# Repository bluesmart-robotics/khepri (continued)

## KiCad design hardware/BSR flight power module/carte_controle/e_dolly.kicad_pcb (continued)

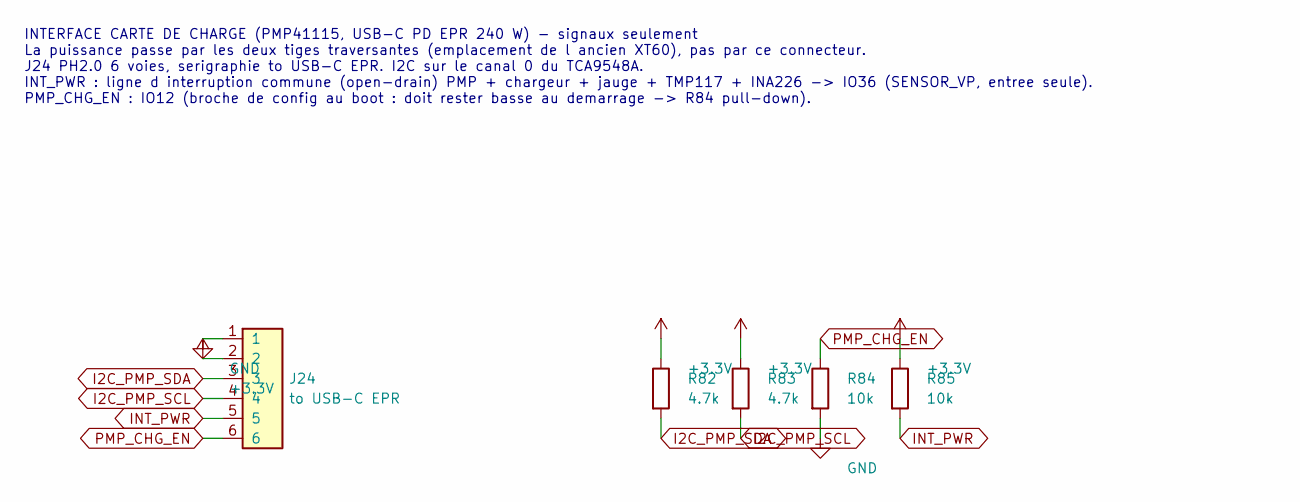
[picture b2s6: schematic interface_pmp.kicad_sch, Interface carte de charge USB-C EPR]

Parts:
J24: to USB-C EPR; JST_PH_B6B-PH-SM4-TB_1x06-1MP_P2.00mm_Vertical
R82, R83: 4.7k; R_0603_1608Metric
R84, R85: 10k; R_0603_1608Metric

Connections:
+3.3V: J24.2, R82.1, R83.1, R85.1; also elsewhere on the board
GND: J24.1, R84.2; also elsewhere on the board
I2C_PMP_SCL: J24.4, R83.2; also elsewhere on the board
I2C_PMP_SDA: J24.3, R82.2; also elsewhere on the board
INT_PWR: J24.5, R85.2; also elsewhere on the board
PMP_CHG_EN: J24.6, R84.1; also elsewhere on the board

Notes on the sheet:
INTERFACE CARTE DE CHARGE (PMP41115, USB-C PD EPR 240 W) - signaux seulement La puissance passe par les deux tiges traversantes (emplacement de l ancien XT60), pas par ce connecteur. J24 PH2.0 6 voies, serigraphie to USB-C EPR. I2C sur le canal 0 du TCA9548A. INT_PWR : ligne d interruption commune 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

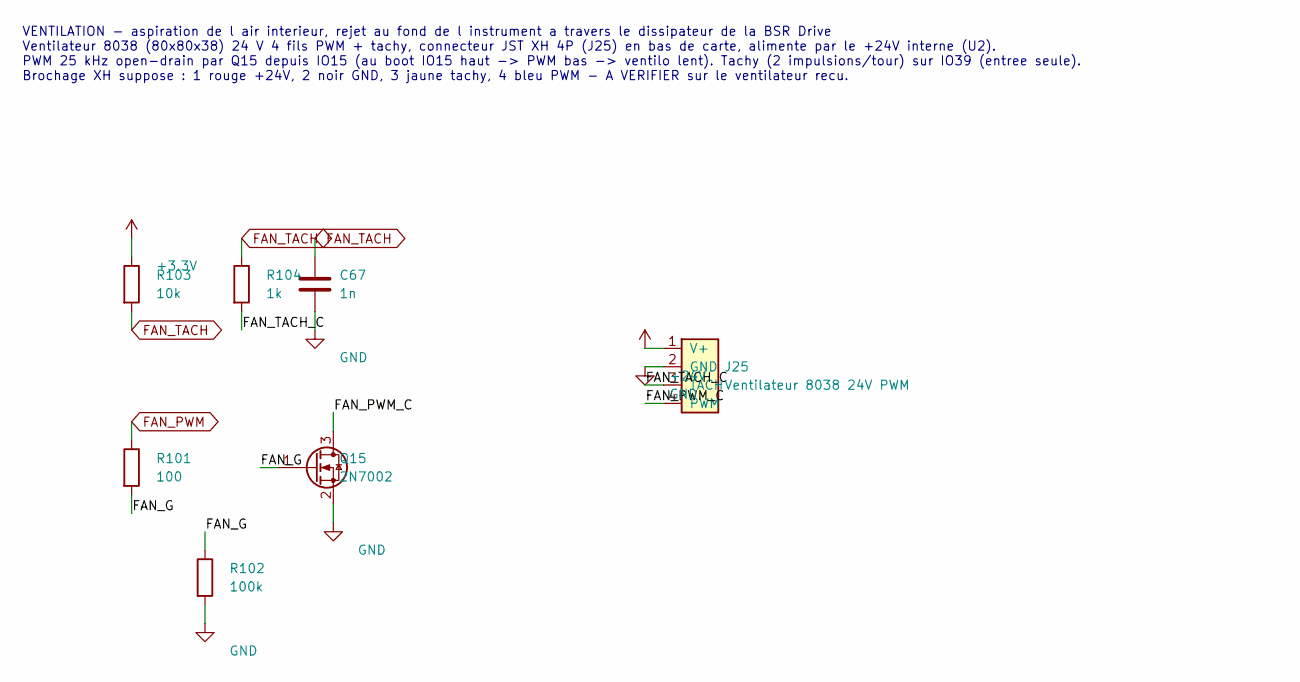
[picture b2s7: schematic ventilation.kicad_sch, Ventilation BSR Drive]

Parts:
C67: 1n; C_0603_1608Metric
J25: Ventilateur 8038 24V PWM; JST_XH_B4B-XH-A_1x04_P2.50mm_Vertical
Q15: 2N7002; SOT-23
R101: 100; R_0603_1608Metric
R102: 100k; R_0603_1608Metric
R103: 10k; R_0603_1608Metric
R104: 1k; R_0603_1608Metric

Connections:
+3.3V: R103.1; also elsewhere on the board
+24V: J25.1 (V+); also elsewhere on the board
/Ventilation/FAN_G: Q15.1 (G), R101.2, R102.1
/Ventilation/FAN_PWM_C: J25.4 (PWM), Q15.3 (D)
/Ventilation/FAN_TACH_C: J25.3 (TACH), R104.2
FAN_PWM: R101.1; also elsewhere on the board
FAN_TACH: C67.1, R103.2, R104.1; also elsewhere on the board
GND: C67.2, J25.2 (GND), Q15.2 (S), R102.2; also elsewhere on the board

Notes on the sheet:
VENTILATION - aspiration de l air interieur, rejet au fond de l instrument a travers le dissipateur de la BSR Drive Ventilateur 8038 (80x80x38) 24 V 4 fils PWM + tachy, connecteur JST XH 4P (J25) en bas de carte, alimente par le +24V interne (U2). PWM 25 kHz open-drain par Q15 depuis IO15 (au boot 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

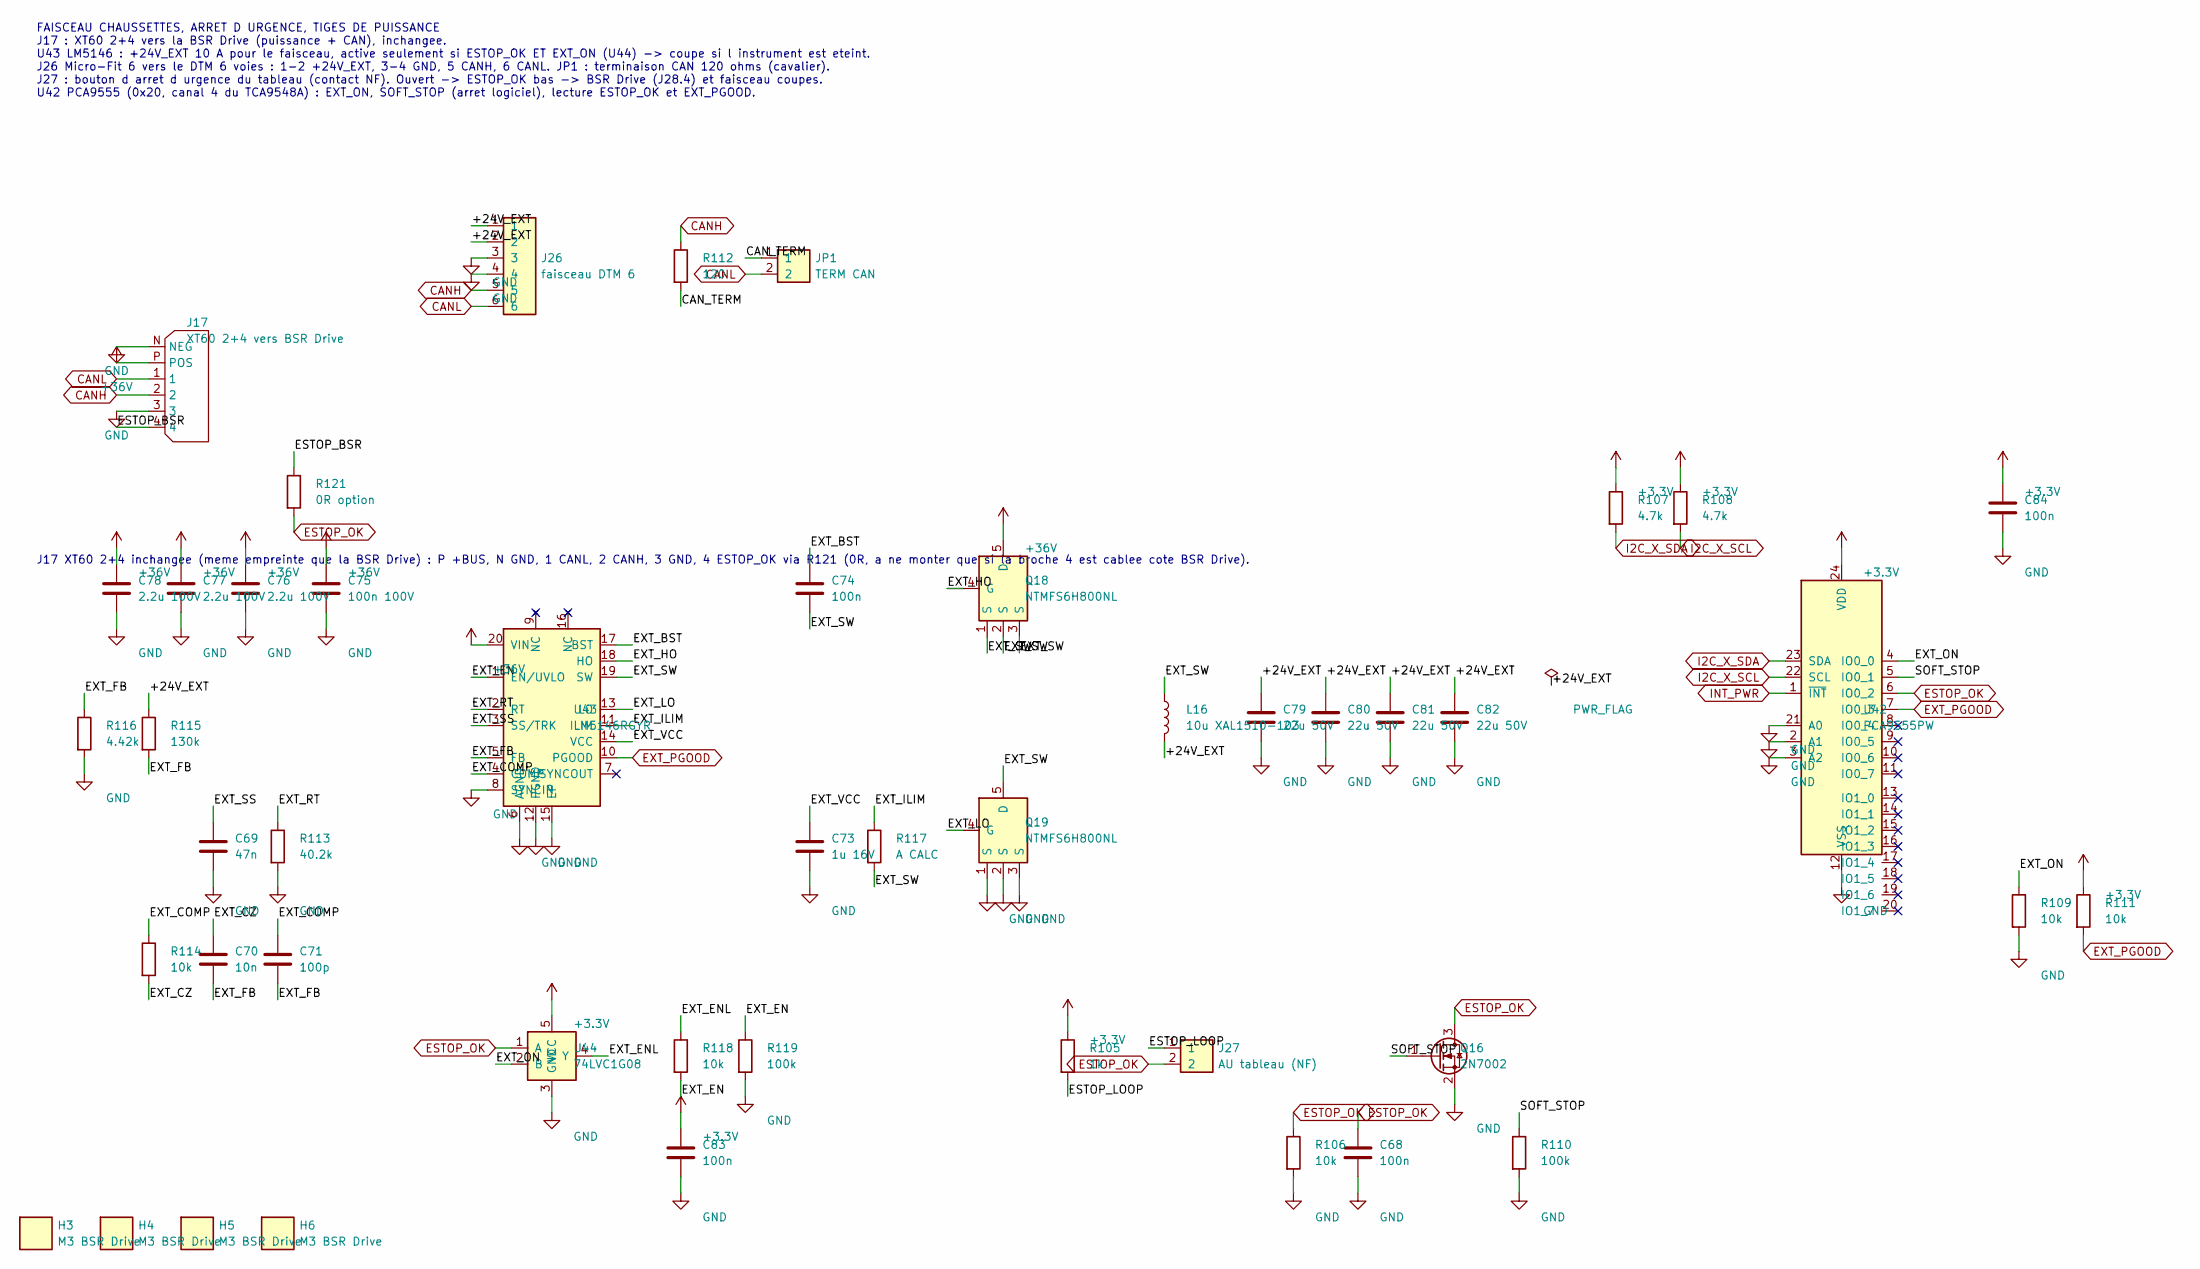
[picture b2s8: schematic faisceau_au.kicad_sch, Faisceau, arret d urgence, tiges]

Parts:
C68, C74, C83, C84: 100n; C_0603_1608Metric
C69: 47n; C_0603_1608Metric
C70: 10n; C_0603_1608Metric
C71: 100p; C_0603_1608Metric
C73: 1u 16V; C_0603_1608Metric
C75: 100n 100V; C_0603_1608Metric
C76, C77, C78: 2.2u 100V; C_1210_3225Metric
C79, C80, C81, C82: 22u 50V; C_1210_3225Metric
H3, H4, H5, H6: M3 BSR Drive; MountingHole_3.2mm_M3
J17: XT60 2+4 vers BSR Drive; AMASS_XT60-F (2+4)
J26: faisceau DTM 6; Molex_Micro-Fit_3.0_43045-0612_2x03_P3.00mm_Vertical
J27: AU tableau (NF); JST_PH_B2B-PH-SM4-TB_1x02-1MP_P2.00mm_Vertical
JP1: TERM CAN; PinHeader_1x02_P2.54mm_Vertical
L16: 10u XAL1510-103; L_Coilcraft_XAL1510-103
Q16: 2N7002; SOT-23
Q18, Q19: NTMFS6H800NL; ONSemi_SO-8FL_488AA
R105: 1k; R_0603_1608Metric
R106, R109, R111, R114, R118: 10k; R_0603_1608Metric
R107, R108: 4.7k; R_0603_1608Metric
R110, R119: 100k; R_0603_1608Metric
R112: 120; R_0603_1608Metric
R113: 40.2k; R_0603_1608Metric
R115: 130k; R_0603_1608Metric
R116: 4.42k; R_0603_1608Metric
R117: A CALC; R_0603_1608Metric
R121: 0R option; R_0603_1608Metric
U42: PCA9555PW; TSSOP-24_4.4x7.8mm_P0.65mm
U43: LM5146RGYR; Texas_RGY_R-PVQFN-N20_EP2.05x3.05mm
U44: 74LVC1G08; SOT-23-5

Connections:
+3.3V: C83.1, C84.1, R105.1, R107.1, R108.1, R111.1, U42.24 (VDD), U44.5 (VCC); also elsewhere on the board
+36V: C75.1, C76.1, C77.1, C78.1, J17.P (POS), Q18.5 (D), U43.20 (VIN); also elsewhere on the board
/Faisceau AU tiges/+24V_EXT: C79.1, C80.1, C81.1, C82.1, J26.1, J26.2, L16.2, R115.1
/Faisceau AU tiges/CAN_TERM: JP1.1, R112.2
/Faisceau AU tiges/ESTOP_BSR: J17.4, R121.1
/Faisceau AU tiges/ESTOP_LOOP: J27.1, R105.2
/Faisceau AU tiges/EXT_BST: C74.1, U43.17 (BST)
/Faisceau AU tiges/EXT_COMP: C71.1, R114.1, U43.4 (COMP)
/Faisceau AU tiges/EXT_CZ: C70.1, R114.2
/Faisceau AU tiges/EXT_EN: R118.2, R119.1, U43.1 (EN/UVLO)
/Faisceau AU tiges/EXT_ENL: R118.1, U44.4 (Y)
/Faisceau AU tiges/EXT_FB: C70.2, C71.2, R115.2, R116.1, U43.5 (FB)
/Faisceau AU tiges/EXT_HO: Q18.4 (G), U43.18 (HO)
/Faisceau AU tiges/EXT_ILIM: R117.1, U43.11 (ILIM)
/Faisceau AU tiges/EXT_LO: Q19.4 (G), U43.13 (LO)
/Faisceau AU tiges/EXT_ON: R109.1, U42.4 (IO0_0), U44.2 (B)
/Faisceau AU tiges/EXT_RT: R113.1, U43.2 (RT)
/Faisceau AU tiges/EXT_SS: C69.1, U43.3 (SS/TRK)
/Faisceau AU tiges/EXT_SW: C74.2, L16.1, Q18.1 (S), Q18.2 (S), Q18.3 (S), Q19.5 (D), R117.2, U43.19 (SW)
/Faisceau AU tiges/EXT_VCC: C73.1, U43.14 (VCC)
/Faisceau AU tiges/SOFT_STOP: Q16.1 (G), R110.1, U42.5 (IO0_1)
CANH: J17.2, J26.5, R112.1; also elsewhere on the board
CANL: J17.1, J26.6, JP1.2; also elsewhere on the board
ESTOP_OK: C68.1, J27.2, Q16.3 (D), R106.1, R121.2, U42.6 (IO0_2), U44.1 (A)
EXT_PGOOD: R111.2, U42.7 (IO0_3), U43.10 (PGOOD)
GND: C68.2, C69.2, C73.2, C75.2, C76.2, C77.2, C78.2, C79.2, C80.2, C81.2, C82.2, C83.2, C84.2, J17.3, J17.N (NEG), J26.3, J26.4, Q16.2 (S), Q19.1 (S), Q19.2 (S), Q19.3 (S), R106.2, R109.2, R110.2, R113.2, R116.2, R119.2, U42.2 (A1), U42.3 (A2), U42.12 (VSS), U42.21 (A0), U43.6 (AGND), U43.8 (SYNCIN), U43.12 (PGND), U43.15 (EP), U43.21, U44.3 (GND); also elsewhere on the board
I2C_X_SCL: R108.2, U42.22 (SCL); also elsewhere on the board
I2C_X_SDA: R107.2, U42.23 (SDA); also elsewhere on the board
INT_PWR: U42.1 (~INT); also elsewhere on the board

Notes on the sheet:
FAISCEAU CHAUSSETTES, ARRET D URGENCE, TIGES DE PUISSANCE J17 : XT60 2+4 vers la BSR Drive (puissance + CAN), inchangee. U43 LM5146 : +24V_EXT 10 A pour le faisceau, active seulement si ESTOP_OK ET EXT_ON (U44) -> coupe si l instrument est eteint. J26 Micro-Fit 6 vers le DTM 6 voies : 1-2 +24V_EXT,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
J17 XT60 2+4 inchangee (meme empreinte que la BSR Drive) : P +BUS, N GND, 1 CANL, 2 CANH, 3 GND, 4 ESTOP_OK via R121 (0R, a ne monter que si la broche 4 est cablee cote BSR Drive).

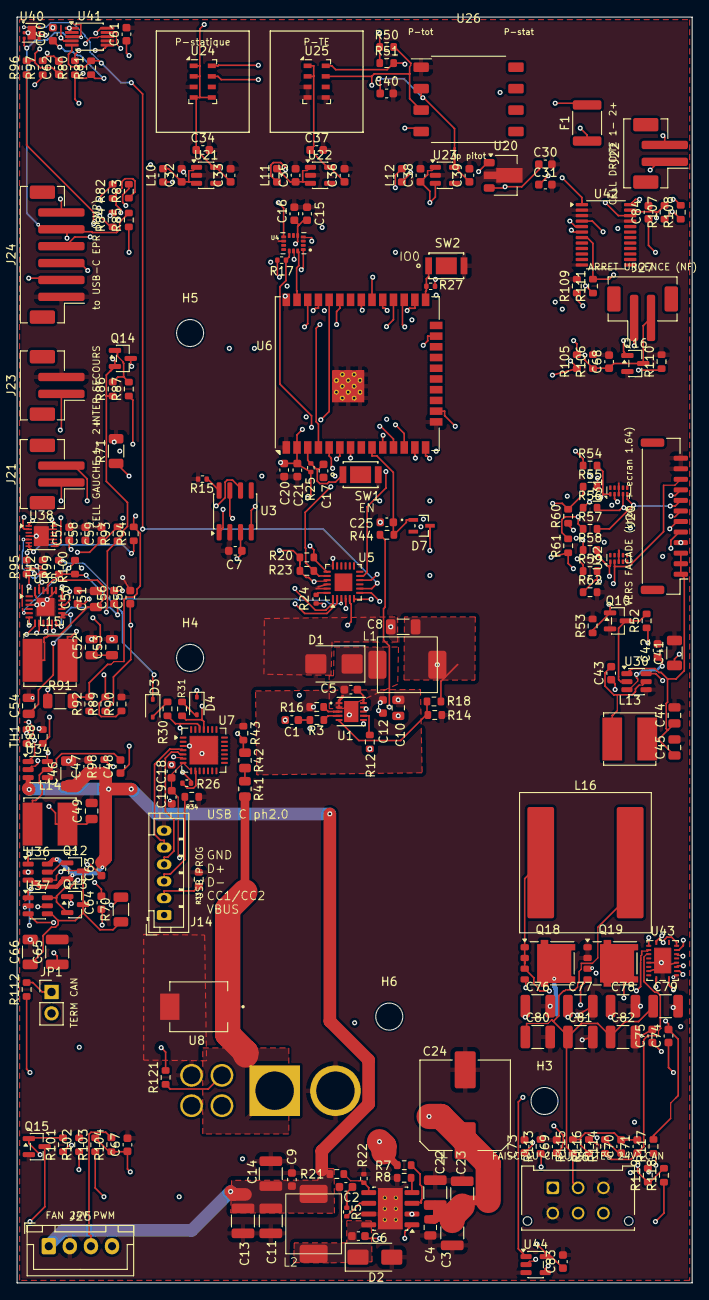
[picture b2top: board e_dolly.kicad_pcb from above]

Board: 4 copper layers, 80.0 x 150.0 mm, 231 parts (1 on the bottom side), 142 nets.

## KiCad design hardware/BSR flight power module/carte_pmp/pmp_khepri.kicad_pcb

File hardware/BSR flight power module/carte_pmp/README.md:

# Carte de charge PMP — version KHEPRI empilable

Chargeur USB-C EPR 240 W dérivé du design TI **PMP41115** (TPS26750 + BQ25756),
repris du dépôt `bluesmart-robotics/batterie` (`chargeur_pmp41115/`, Altium) et
converti en KiCad 9 pour être empilé au-dessus de la carte de contrôle et de la
BSR Drive. **Le dépôt `batterie` n'est pas modifié** (E-dolly garde sa version).

## Ce qui a été fait (04/11/2026)

1. **Import Altium → KiCad** (`PMP41115.PcbDoc`, importeur Altium de KiCad),
   puis ouverture et sauvegarde en KiCad 9.
2. **Bloc PMP tourné de −90°** et placé dans le contour de la pile : bloc
   d'origine 103 × 47 mm maintenant en x 134,5 → 181,3, y 31,0 → 134,0. Le
   connecteur USB-C J1 est en haut, à ≈ 7 mm du bord haut (bord à y 28,85).
   L'ancien contour Altium est conservé sur la couche `User.9` comme repère.
3. **Contour agrandi à 80 × 150 mm**, **même repère que la carte de contrôle**
   (x 104 → 184, y 28,85 → 178,85) : les deux fichiers KiCad se superposent
   sans décalage.
4. **XT60 2+4 J7**, même empreinte et **même position que J17 de la carte de
   contrôle** (138,125 ; 156,075), côté dessous (B.Cu). Liaison bidirectionnelle
   vers le pack : P = `BAT` (sortie/entrée batterie du BQ25756), N et broche 3 =
   GND, broches 1, 2, 4 (CAN, ESTOP) non reliées sur cette carte.
   Liaison en pistes de 1,5 mm (BAT sur B.Cu ≈ 23 mm, GND) : **à remplacer
   par des zones de cuivre** pour 5 A permanents.
5. **Connecteur de communication J8**, JST PH 6 voies (même empreinte que J24
   de la carte de contrôle, même position x 108,75 ; y 57), câble court entre
   les deux cartes :

   | J8 | Signal carte de contrôle (J24) | Net sur la PMP |
   |---|---|---|
   | 1 | GND | GND |
   | 2 | +3,3 V | `3V3_CTRL` — **non relié** (ne pas raccorder au LDO_3V3 de la PMP) |
   | 3 | SDA canal 0 | `I2Ct_SDA` (I²C cible du TPS26750, comme J6) |
   | 4 | SCL canal 0 | `I2Ct_SCL` |
   | 5 | INT_PWR | `~{I2Ct_IRQ}` (drain ouvert) |
   | 6 | CHG_EN | `CHG_EN` — **non relié** : choisir la broche (EN du BQ25756, ILIM_HIZ ou GPIO du TPS26750) |

6. **Trous M3** H11 à H15 aux positions des trous de la BSR Drive qui tombent
   hors du bloc PMP : (124,53 ; 66,30), (124,53 ; 104,80), (124,53 ; 147,30),
   (148,13 ; 147,30), (166,53 ; 157,30). Les trous BSR (148,13 ; 66,30) et
   (148,13 ; 104,80) tombent dans le bloc PMP et n'ont pas été percés (choix
   validé : garder le routage puissance d'origine).

## À reprendre par l'ingénieur

1. **Schéma** : il reste en Altium dans le dépôt `batterie`. J7, J8, H11–H15 et
   leurs nets n'existent que dans ce PCB. À reporter dans un schéma (ou importer
   les SchDoc dans KiCad) avant toute mise à jour schéma → PCB.
2. **Erreurs d'import Altium à vérifier contre le PcbDoc d'origine** (DRC KiCad :
   ≈ 1 060 erreurs, aucune ne vient des ajouts ci-dessus) :
   - pastilles « complex pad stack » non importées correctement : pastilles
     thermiques sans net de Q4, Q5, Q6, Q7 et U5 → 81 « courts-circuits »
     avec les vias VSYS, P_OUT, SW1, SW2 ;
   - 199 vias 0,3/0,2 mm d'Altium hors des règles par défaut de KiCad
     (diamètre, anneau) : ajuster les règles ou les vias ;
   - U8.5 (GND) et U1.28/29 (PP5V) non reliés après import.
3. Remplacer les pistes BAT / GND de J7 par des zones, ajouter des vias en
   parallèle.
4. Raccorder J8.2 et J8.6 (tableau ci-dessus).
5. Modèles 3D des composants : non repris de l'Altium, le STEP de cette carte
   ne montre que le circuit nu et les composants ajoutés.

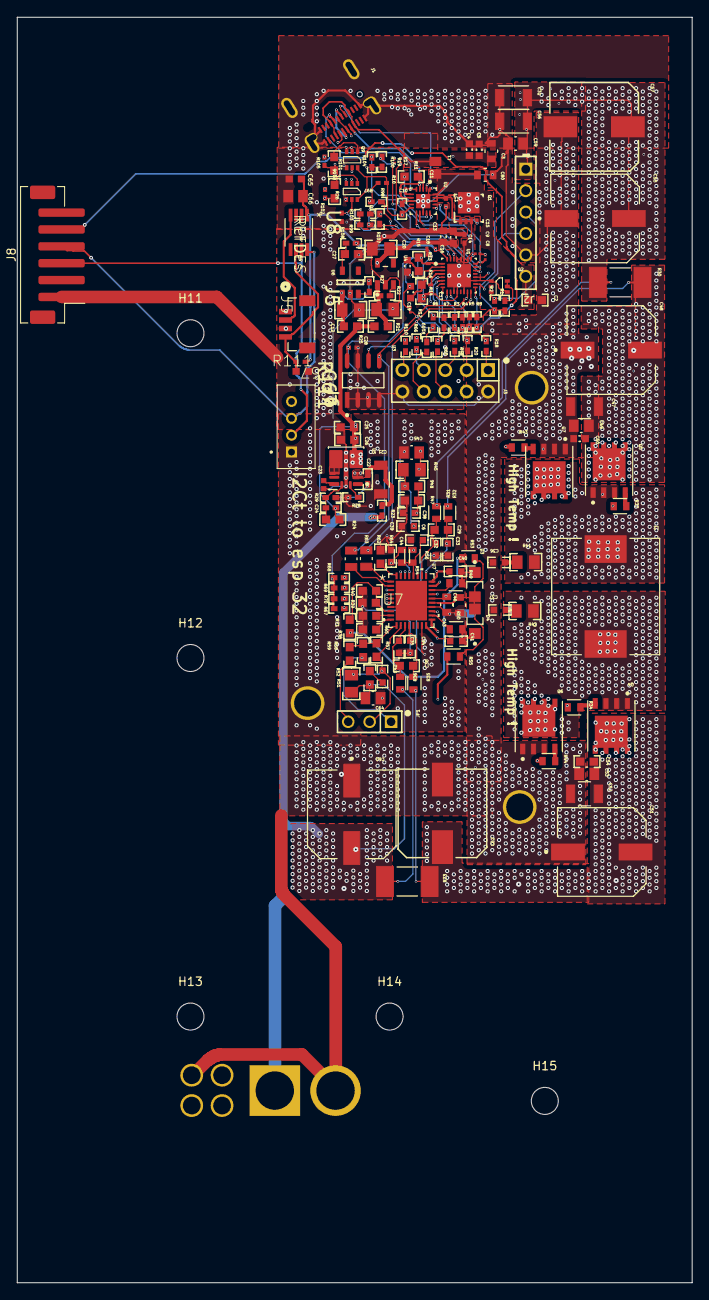
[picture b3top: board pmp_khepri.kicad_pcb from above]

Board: 4 copper layers, 80.0 x 150.0 mm, 181 parts (1 on the bottom side), 113 nets.

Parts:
C1, C15: C1005X5R1H104K050BB; 0402L
C2, C11: GRM188R72A104KA35J; 0603
C3, C80: C2012X5R2A475K125AC; FP-C2012X5R2A475K125AC_0805-MFG
C4, C5: C0603X103K1RACTU; 0603L
C6, C32, C33, C34, C35, C38, C39, C44: HMK107B7104KAHT; 0603_HV
C8, C9: CGA1A2X7R1H221K030BA; 0201_033L
C10: 885012205037; 0402
C12: CGA2B3X7R1H104K050BB; 0402L
C13, C14: GRM188R61E106MA73D; 0603L
C16, C17, C18: CL05A106MP5NUNC; 0402_070
C19, C20, C28: C2012X7S2A105K125AB; 0805_HV
C21: C3216X7S2A225K160AB; 1206_180
C22: GRM155R62A104KE14D; 0402
C23: 0402YD105KAT2A; FP-0402YD105KAT2A_0402-IPC_B
C24: C0402C100C8GACTU; 0402
C25, C26: CL10A226MP8NUNE; 0603
C27: CGA3E3X5R1A225K080AB; 0603
C29, C30: C0603C474K4RACTU; 0603
C31, C56: GCJ32DC72A475KE01L; FP-GCJ32DC72A475KE01L_1210-MFG
C36, C37: 06031A330JAT2A; 0603_HV
C40, C41: 06033C104KAT2A; 0603_HV
C42: GCM1885C2A101JA16D; 0603_HV
C43, C46: CGA4J1X7R1E475K125AE; FP-CGA4J1X7R1E475K125AE_0805-MFG
C45, C49, C53, C59, C64: 08051C105K4Z2A; 0805_150
C47, C52: C3225X7R2A106K250AC; FP-C3225X7R2A106K250AC_1210-MFG
C48, C51, C55, C60: PCR1J101MCL1GS; FP-PCR1J101MCL1GS_SMD_RADIAL-MFG
C50: HMK107B7104KAHT; 0603L
C54: CGA3E2C0G2A101J080AA; 0603
C57, C62: EEHZC1J560P; SM_RADIAL_10BMM
C65, C67: 0.1u; G-188_MUR
C66: 1u; CAPC2012X145N
D3, D4: V1FM10-M3/H; FP-V1FM10-M3-H_DO-219AB-MFG
H11, H12, H13, H14, H15: M3 BSR Drive; MountingHole_3.2mm_M3
J1: DX07S024JJ2R1300; JAE_DX07S024JJ2R1300
J2: SSW-106-01-T-S; Samtec_SSW-106-01-x-S
J3: PEC05DAAN; CONN_PEC05DAAN
J5: BM04B-SRSS-TB; CONN4_BM04B-SRSS_JST
J6: B4B-PH-K-S; JST_B4B-PH-K-S
J7: AMASS_XT60-F (2+4)
J8: to USB-C EPR; JST_PH_B6B-PH-SM4-TB_1x06-1MP_P2.00mm_Vertical
JP1: PEC03SAAN; CONN_PEC03SAAN
L1: 742792021; 0805L
L2: CMLB135T-100MS; FP-CMLB135T-100MS_SMT2_13MM45_12Mm6-MFG
Q1: CSD18543Q3A; DNH0008A
Q2, Q3, Q9: 2N7002DW; SOT-363
Q4, Q5, Q6, Q7: SIR880BDP-T1-RE3; FP-SIR880BDP-T1-RE3_SO-8-MFG
R1, R2: ERJ-2RKF1001X; 0402
R3, R4, R6, R7: RC0402FR-072K2L; 0402
R5, R8: CRCW040210K0DHEDP; 0402
R10, R11, R17, R19: CRCW02010000Z0ED; 0201L
R12: RC0201FS-7D100KL; 0201L
R13, R16: RT0603BRD07470RL; 0603
R14, R15: RC0603FR-07100KL; 0603L
R18, R20, R48, R60, R66, R98, R99, R100, R103, R104, R107, R109, R110: RC0402JR-070RL; 0402
R21, R25: RC0603JR-070RL; 0603
R22, R23, R26, R27: CMP-0027004-2; 0402
R24: RT0603BRD0760K4L; 0603
R28: CRCW040219K6FKED; 0402
R29: ERJ-2RKF1002X; 0402
R30, R33: WSL25125L000FEA; FP-WSL25125L000FEA_2512-MFG
R31, R32, R35, R36: CRCW060310R0FKEB; FP-CRCW060310R0FKEB_0603-MFG
R34, R37, R43, R44, R49, R50, R53, R54, R55, R56: CRCW06030000Z0EA; FP-CRCW06031R50FKEAHP_0603-MFG
R38: RC0603FR-075K23L; 0603
R39: ERJ-3EKF1002V; 0603
R40: RC0603FR-0730K1L; 0603
R41, R42: RC0805JR-072R2L; 0805_HV
R45: CRCW08051M00FKEAC; 0805_HV
R46: RT0603BRD07383KL; 0603
R47: RT0603BRD0731K2L; 0603
R51: CRCW06031R10JNEA; 0603
R52: ERJ-PB6B2493V; 0805_HV
R57: RT0603BRD0713K7L; 0603
R58: RT0603BRD0730K5L; 0603
R59: RT0603BRD0713KL; 0603
R62: RC0603FR-07100KL; 0603
R63, R64: CRCW08050000Z0EA; FP-CRCW080510R0JNEAHP_0805-MFG
R65: RC0603FR-073K6L; 0603
R67, R68, R69, R70: RC0402FR-0710K5L; 0402
R71: RG1608P-822-B-T5; 0603
R97, R108: RC1005F104CS; 0402L
R101, R102: RG1608P-2493-B-T5; 0603
R105, R106: ERJ-2RKF1004X; 0402L
R111: 10k; RC0402N_VIS
U1: TPS26750RSMR; RSM0032B-MFG
U2: TPD4S480RUKR; RUK0020B-MFG
U3: CAT24C512WI-GT3; FP-CAT24C512WI-GT3_SOIC8-IPC_C
U4: TPS7A2450DBVR; DBV0005A-MFG
U5: TPSM365R6RDNR; RDN0011A-MFG
U6: TPS76333DBVR; DBV0005A_N
U7: BQ25756RRVR; VQFN36_RRV_TEX
U8: EMC2101-R-ACZL-TR; MSOP8_MC_MCH

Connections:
/INT: R68.1, U7.3
/PG: R67.1, U7.6
ACN: C29.2, C33.1, R32.1, U7.29
ACOV: C39.1, R46.1, R47.2, U7.35
ACP: C29.1, C32.1, R31.1, U7.30
ACUV: C38.1, R45.1, R46.2, U7.34
ADCIN1: R13.1, R15.2, U1.2
ADCIN2: R14.1, R16.2, U1.3
BAT: C60.2, C64.1, J7.P (POS), R23.2, R33.2, R36.1, R51.2, R52.2
BTST1: R49.1, U7.26
BTST2: R50.1, U7.20
CC1: C9.1, U1.24, U2.12
CC2: C8.1, U1.25, U2.11
C_CC1: J1.A5, R10.2, U2.4
C_CC2: J1.B5, R11.2, U2.5
C_SBU1: J1.A8, U2.1
C_SBU2: J1.B8, U2.2
DRV_SUP: C43.1, D3.2, D4.2, R53.2, R55.2, U7.23
EPR_EN: R48.1, U1.7, U2.16
E_Fuse Source: J2.4, U1.18
FAN_PWM: J5.2, U8.4
FAN_TACH: C67.2, J5.4, R111.1, U8.6
FB: C42.2, JP1.2, R52.1, R57.2, U7.12
FBG: R57.1, R58.1, R59.1, U7.11
FSW_SYNC: R62.2, U7.36
GND: C1.2, C2.2, C3.1, C4.2, C5.2, C6.1, C8.2, C9.2, C10.2, C11.1, C12.2, C13.2, C14.2, C15.2, C16.1, C17.1, C18.2, C19.2, C20.2, C21.2, C22.2, C23.2, C25.2, C26.2, C27.2, C28.2, C31.1, C32.2, C33.2, C34.2, C35.2, C36.2, C37.2, C38.2, C39.2, C43.2, C44.1, C45.2, C46.2, C47.1, C48.1, C49.2, C50.2, C51.1, C52.1, C53.2, C54.2, C55.1, C56.2, C57.2, C59.2, C60.1, C62.2, C64.2, C65.1, C66.1, C67.1, C80.1, J1.A1, J1.A12, J1.B1, J1.B12, J1.S1, J1.S2, J1.S3, J1.S4, J2.5, J3.2, J3.10, J5.3, J6.1, J7.3, J7.N (NEG), J8.1, Q2.1, Q2.4, Q3.4, Q6.1, Q6.2, Q6.3, Q7.1, Q7.2, Q7.3, Q9.4, R15.1, R16.1, R28.1, R29.1, R39.1, R40.1, R47.1, R62.1, R65.1, R71.1, R108.1, U1.11, U1.12, U1.14, U1.19, U1.33, U2.8, U2.13, U2.18, U2.21, U3.1, U3.2, U3.3, U3.4, U3.7, U4.2, U5.10, U6.2, U7.7, U7.17, U7.22, U7.37, U8.5
GPIO0: R110.1, U1.5
GPIO1: R66.1, U1.6
GPIO4: R17.1, R99.1, U1.22
GPIO5: R19.1, R100.2, U1.23
GPIO6: R98.1, U1.31
GPIO7: R107.1, U1.30
GPIO_NF: Q3.5, Q9.5, R107.2, R108.2
GPIO_PF: Q3.2, Q9.2, R97.1, R98.2
HIDRV1: R37.2, U7.27
HIDRV2: R34.2, U7.19
I2Cc_SCL: R6.1, R64.2, R109.2, U1.16, U3.6
I2Cc_SDA: R7.1, R12.1, R60.2, R63.2, U1.15, U3.5
I2Ct_SCL: J6.3, J8.4, R3.1, R18.1, U1.9, U8.8
I2Ct_SDA: J6.2, J8.3, R4.1, R20.1, U1.8, U8.7
ICHG: R71.2, U7.9
ILIM_HIZ: R65.2, U7.10
LDO_1V5: C17.2, U1.4
LDO_3V3: C10.1, C12.1, C16.2, J2.2, Q3.6, Q9.6, R1.2, R2.2, R3.2, R4.2, R5.2, R6.2, R7.2, R8.2, R12.2, R13.2, R14.2, R67.2, R68.2, R69.2, R70.2, R97.2, U1.1, U2.10, U3.8
LODRV1: R43.1, U7.25
LODRV2: R44.1, U7.21
NetC6_2: C6.2, R54.2, R56.2, U7.32
NetC11_2: C11.2, U2.3
NetC19_1: C19.1, R21.2, R22.2, U4.1
NetC21_1: C21.1, C22.1, R23.1, U5.2, U5.3
NetC23_1: C23.1, U5.8
NetC24_2: C24.2, R24.1, R29.2, U5.9
NetC27_1: C27.1, R26.2, U6.5
NetC28_1: C28.1, R25.2, R27.2, U6.1
NetC36_1: C36.1, R41.1
NetC37_1: C37.1, R42.1
NetC40_2: C40.2, D3.1, R49.2
NetC41_1: C41.1, D4.1, R50.2
NetC42_1: C42.1, R51.1
NetJ3_1: J3.1, R18.2
NetJ3_3: J3.3, R20.2
NetJ3_5: J3.5, R48.2
NetJ3_6: J3.6, R60.1
NetJ3_7: J3.7, R66.2
NetJ3_8: J3.8, R109.1
NetJ3_9: J3.9, R110.2
NetJP1_1: JP1.1, R58.2
NetJP1_3: JP1.3, R59.2
NetQ1_4: Q1.4, U2.17
NetQ2_2: Q2.2, U1.20
NetQ2_5: Q2.5, Q2.6, R1.1
NetQ3_1: Q3.1, R102.2
NetQ3_3: Q3.3, R106.1
NetQ4_4: Q4.4, R34.1
NetQ5_4: Q5.4, R37.1
NetQ6_4: Q6.4, R44.2
NetQ7_4: Q7.4, R43.2
NetQ9_1: Q9.1, R101.2
NetQ9_3: Q9.3, R105.1
NetR10_1: R10.1, U2.7
NetR11_1: R11.1, U2.6
NetR22_1: R22.1, U4.3
NetR27_1: R27.1, U6.3
NetR28_2: R28.2, U5.11
NetR63_1: R63.1, U7.2
NetR64_1: R64.1, U7.1
NetR99_2: R99.2, R101.1, R103.2, R105.2
NetR100_1: R100.1, R102.1, R104.1, R106.2
NetU5_5: U5.5, U5.6
PD_D_N: J1.A7, J1.B7, R19.2
PD_D_P: J1.A6, J1.B6, R17.2
PP5V: C13.1, C14.1, C20.1, J5.1, U1.28, U1.29, U4.5
PP7V: C24.1, C25.1, C26.1, R21.1, R24.2, R25.1, R55.1, U5.4
PPHV: C31.2, C44.2, C45.1, C55.2, C56.1, C57.1, C59.1, J2.1, R30.1, R31.2, R45.2, R54.1, U7.33
PP_EN: J2.3, Q2.3, R2.1
P_OUT: C51.2, C52.2, C53.1, C54.1, C62.1, Q4.5-6-7-8, R33.1, R35.1
REGN: C46.1, R38.2, R53.1, U7.24
SBU1: R103.1, U2.15
SBU2: R104.2, U2.14
SRN: C30.2, C35.1, R36.2, U7.13
SRP: C30.1, C34.1, R35.2, U7.14
STAT1: R69.1, U7.4
STAT2: R70.1, U7.5
SW1: C40.1, L2.1, Q5.1, Q5.2, Q5.3, Q7.5-6-7-8, R41.2, U7.28
SW2: C41.2, L2.2, Q4.1, Q4.2, Q4.3, Q6.5-6-7-8, R42.2, U7.18
TS: R38.1, R39.2, R40.2, U7.8
VBUS: C2.1, C80.2, J2.6, L1.1, Q1.5, Q1.6, Q1.7, Q1.8, Q1.9, R56.1, U2.20
VBUS_C: C3.2, C4.1, C5.1, J1.A4, J1.A9, J1.B4, J1.B9, L1.2
VBUS_LV: C1.1, C15.1, Q1.1, Q1.2, Q1.3, U1.26, U1.27, U2.19
VIN_3V3: C18.1, C65.2, C66.2, R26.1, R111.2, U1.32, U8.1
VSYS: C47.2, C48.2, C49.1, C50.1, Q5.5-6-7-8, R30.2, R32.2
~I2Cc_IRQ: R8.1, U1.17
~I2Ct_IRQ: J8.5, R5.1, U1.10

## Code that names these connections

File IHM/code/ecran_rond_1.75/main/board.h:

/*
 * board.h — Waveshare ESP32-S3-Touch-AMOLED-1.75 (-B / -G) : brochage utilisé par l'écran pilote.
 * Source : HARDWARE_REFERENCE.md et BSP Waveshare (esp32_s3_touch_amoled_1_75.h).
 */
#pragma once

#include "driver/gpio.h"
#include "driver/uart.h"

/* Écran AMOLED 1,75" 466×466, contrôleur CO5300 en QSPI */
#define PIN_LCD_CS    GPIO_NUM_12
#define PIN_LCD_PCLK  GPIO_NUM_38
#define PIN_LCD_D0    GPIO_NUM_4
#define PIN_LCD_D1    GPIO_NUM_5
#define PIN_LCD_D2    GPIO_NUM_6
#define PIN_LCD_D3    GPIO_NUM_7
#define PIN_LCD_RST   GPIO_NUM_39
#define PIN_LCD_TE    GPIO_NUM_13
#define LCD_W         466
#define LCD_H         466
#define LCD_X_GAP     6 /* la dalle commence à la colonne 6 du CO5300 */

/* Tactile CST9217 (I2C 0x5A) */
#define PIN_TP_INT    GPIO_NUM_11
#define PIN_TP_RST    GPIO_NUM_40

/* Bus I2C commun : SCL 14, SDA 15 (voir components/i2c_bsp) */
#define I2C_ADDR_TCA9554 0x20
#define I2C_ADDR_QMI8658 0x6B
#define I2C_ADDR_CST9217 0x5A

/* Extenseur TCA9554 */
#define EXIO_PWR_BTN  4 /* P4 : SYS_OUT, haut tant que PWR est appuyé (Waveshare seulement) */
#define EXIO_GPS_RST  7 /* P7 : reset du LC76G (version -G) ou du GPS externe (carte BSR, J7 broche 5) */

/* Carte BSR (hardware/BSR flight power module/ecran_rond_1.75) : bouton BOOT en guise de bouton
 * utilisateur, UART1 vers la carte façade sur le connecteur JST J2 (5 V, GND, TX, RX) */
#define PIN_BTN_BOOT      GPIO_NUM_0  /* actif bas, pull-up externe */
#define PIN_FACADE_TX     GPIO_NUM_17
#define PIN_FACADE_RX     GPIO_NUM_18
#define FACADE_UART_NUM   UART_NUM_1
#define PIN_GPS_PPS       GPIO_NUM_21 /* carte BSR : 1PPS du module GPS externe (J7 broche 6), GPS en I2C */

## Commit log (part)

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2026-03-14 controler screen + controller espnow
2026-04-01 screen 0
